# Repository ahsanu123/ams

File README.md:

<p>

</p>

 <details>
   <summary><h2>Shema</h2></summary>

 </details>
 
<sub> Work In Progress, Made With ❤️ By Ah...</sub>

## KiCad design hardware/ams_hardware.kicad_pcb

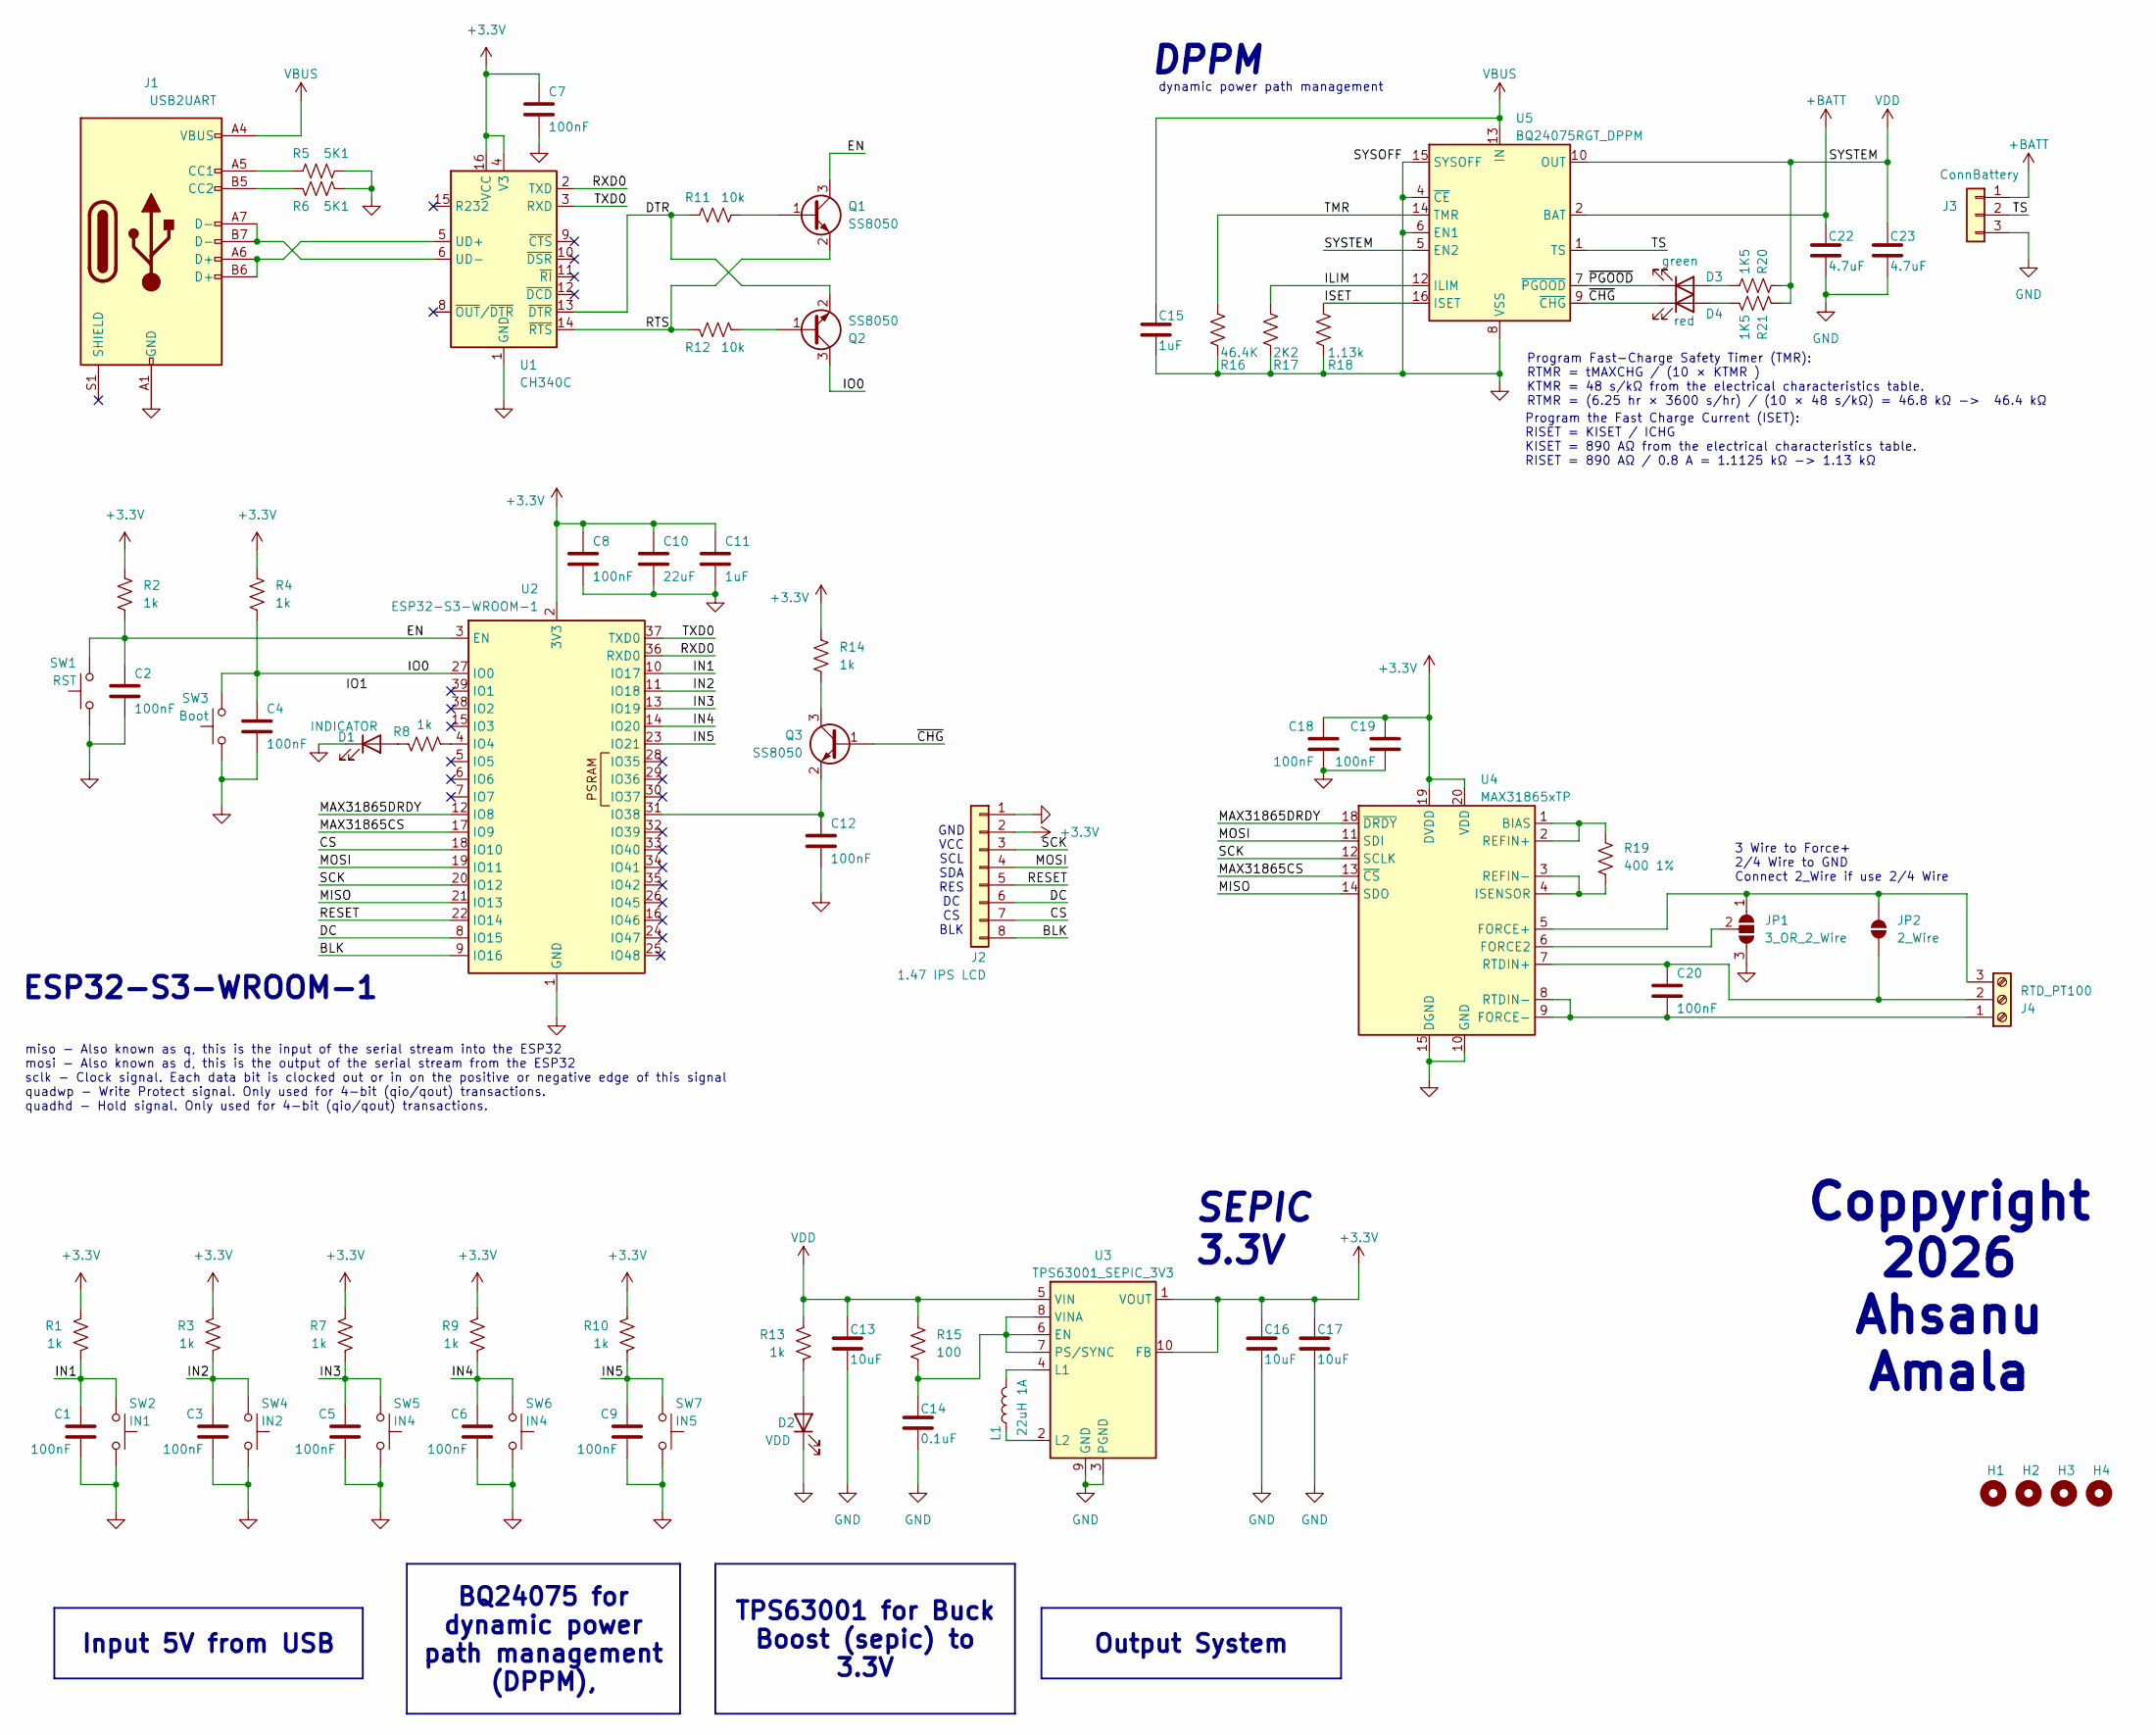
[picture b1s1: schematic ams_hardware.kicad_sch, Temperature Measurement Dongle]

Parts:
C1, C2, C3, C4, C5, C6, C7, C8, C9, C12, C18, C19, C20: 100nF; C_0805_2012Metric_Pad1.18x1.45mm_HandSolder
C10: 22uF; C_0805_2012Metric_Pad1.18x1.45mm_HandSolder
C11, C15: 1uF; C_0805_2012Metric_Pad1.18x1.45mm_HandSolder
C13, C16, C17: 10uF; C_0805_2012Metric_Pad1.18x1.45mm_HandSolder
C14: 0.1uF; C_0805_2012Metric_Pad1.18x1.45mm_HandSolder
C22, C23: 4.7uF; C_0805_2012Metric_Pad1.18x1.45mm_HandSolder
D1: INDICATOR; LED_1206_3216Metric_Pad1.42x1.75mm_HandSolder
D2: VDD; LED_1206_3216Metric_Pad1.42x1.75mm_HandSolder
D3: green; LED_0805_2012Metric_Pad1.15x1.40mm_HandSolder
D4: red; LED_0805_2012Metric_Pad1.15x1.40mm_HandSolder
H1, H2, H3, H4: MountingHole; MountingHole_2mm
J1: USB2UART; USB_C_Receptacle_GCT_USB4110
J2: 1.47 IPS LCD; PinHeader_1x08_P2.54mm_Vertical
J3: ConnBattery; PinHeader_1x03_P2.54mm_Vertical
J4: RTD_PT100; TerminalBlock_Phoenix_PT-1,5-3-5.0-H_1x03_P5.00mm_Horizontal
JP1: 3_OR_2_Wire; SolderJumper-3_P1.3mm_Open_RoundedPad1.0x1.5mm
JP2: 2_Wire; SolderJumper-2_P1.3mm_Open_TrianglePad1.0x1.5mm
L1: 22uH 1A; L_Bourns_SRP7028A_7.3x6.6mm
Q1, Q2, Q3: SS8050; SOT-23_Handsoldering
R1, R2, R3, R4, R7, R8, R9, R10, R13, R14: 1k; R_0805_2012Metric_Pad1.20x1.40mm_HandSolder
R5, R6: 5K1; R_0805_2012Metric_Pad1.20x1.40mm_HandSolder
R11, R12: 10k; R_0805_2012Metric_Pad1.20x1.40mm_HandSolder
R15: 100; R_0805_2012Metric_Pad1.20x1.40mm_HandSolder
R16: 46.4K; R_0805_2012Metric_Pad1.20x1.40mm_HandSolder
R17: 2K2; R_0805_2012Metric_Pad1.20x1.40mm_HandSolder
R18: 1.13k; R_0805_2012Metric_Pad1.20x1.40mm_HandSolder
R19: 400 1%; R_0805_2012Metric_Pad1.20x1.40mm_HandSolder
R20, R21: 1K5; R_0805_2012Metric_Pad1.20x1.40mm_HandSolder
SW1: RST; SW_SPST_PTS810
SW2: IN1; SW_SPST_Omron_B3FS-100xP
SW3: Boot; SW_SPST_PTS810
SW4: IN2; SW_SPST_Omron_B3FS-100xP
SW5, SW6: IN4; SW_SPST_Omron_B3FS-100xP
SW7: IN5; SW_SPST_Omron_B3FS-100xP
U1: CH340C; SOIC-16_3.9x9.9mm_P1.27mm
U2: ESP32-S3-WROOM-1
U3: TPS63001_SEPIC_3V3; Texas_DRC0010J_ThermalVias
U4: MAX31865xTP; TQFN-20-1EP_5x5mm_P0.65mm_EP3.25x3.25mm
U5: BQ24075RGT_DPPM; VQFN-16-1EP_3x3mm_P0.5mm_EP1.6x1.6mm

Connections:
+3.3V: C7.1, C8.1, C10.1, C11.1, C16.1, C17.1, C18.1, C19.1, J2.2, R1.1, R2.1, R3.1, R4.1, R7.1, R9.1, R10.1, R14.1, U1.4 (V3), U1.16 (VCC), U2.2 (3V3), U3.1 (VOUT), U3.10 (FB), U4.19 (DVDD), U4.20 (VDD)
+BATT: C22.1, J3.1, U5.2 (BAT), U5.3 (BAT)
/BLK: J2.8, U2.9 (IO16)
/CS: J2.7, U2.18 (IO10)
/DC: J2.6, U2.8 (IO15)
/DTR: Q2.2 (E), R11.2, U1.13 (~DTR)
/EN: C2.1, Q1.3 (C), R2.2, SW1.2, U2.3 (EN)
/ILIM: R17.1, U5.12 (ILIM)
/IN1: C1.1, R1.2, SW2.2, U2.10 (IO17)
/IN2: C3.1, R3.2, SW4.2, U2.11 (IO18)
/IN3: C5.1, R7.2, SW5.2, U2.13 (IO19)
/IN4: C6.1, R9.2, SW6.2, U2.14 (IO20)
/IN5: C9.1, R10.2, SW7.2, U2.23 (IO21)
/IO0: C4.1, Q2.3 (C), R4.2, SW3.2, U2.27 (IO0)
/ISET: R18.1, U5.16 (ISET)
/MAX31865CS: U2.17 (IO9), U4.13 (~CS)
/MAX31865DRDY: U2.12 (IO8), U4.18 (~DRDY)
/MISO: U2.21 (IO13), U4.14 (SDO)
/MOSI: J2.4, U2.19 (IO11), U4.11 (SDI)
/RESET: J2.5, U2.22 (IO14)
/RTS: Q1.2 (E), R12.2, U1.14 (~RTS)
/RXD0: U1.2 (TXD), U2.36 (RXD0)
/SCK: J2.3, U2.20 (IO12), U4.12 (SCLK)
/TMR: R16.1, U5.14 (TMR)
/TS: J3.2, U5.1 (TS)
/TXD0: U1.3 (RXD), U2.37 (TXD0)
/~CHG: D4.1 (K), Q3.1 (B), U5.9 (~CHG)
/~PGOOD: D3.1 (K), U5.7 (~PGOOD)
GND: C1.2, C2.2, C3.2, C4.2, C5.2, C6.2, C7.2, C8.2, C9.2, C10.2, C11.2, C12.2, C13.2, C14.2, C15.2, C16.2, C17.2, C18.2, C19.2, C22.2, C23.2, D1.1 (K), D2.1 (K), J1.A1 (GND), J1.A12 (GND), J1.B1 (GND), J1.B12 (GND), J2.1, J3.3, JP1.3 (B), R5.1, R6.1, R16.2, R17.2, R18.2, SW1.1, SW2.1, SW3.1, SW4.1, SW5.1, SW6.1, SW7.1, U1.1 (GND), U2.1 (GND), U2.40 (GND), U2.41 (GND), U3.3 (PGND), U3.9 (GND), U3.11 (PGND), U4.10 (GND), U4.15 (DGND), U4.16 (GND), U4.21 (GND), U5.4 (~CE), U5.6 (EN1), U5.8 (VSS), U5.15 (SYSOFF), U5.17 (VSS)
unnamed: D1.2 (A), R8.1
unnamed: D2.2 (A), R13.2
unnamed: D3.2 (A), R20.1
unnamed: D4.2 (A), R21.1
unnamed: J1.A5 (CC1), R5.2
unnamed: J1.B5 (CC2), R6.2
unnamed: C20.2, J4.1, U4.8 (RTDIN-), U4.9 (FORCE-)
unnamed: C20.1, J4.2, JP2.1 (A), U4.7 (RTDIN+)
unnamed: J4.3, JP1.1 (A), JP2.2 (B), U4.5 (FORCE+)
unnamed: JP1.2 (C), U4.6 (FORCE2)
unnamed: Q1.1 (B), R11.1
unnamed: Q2.1 (B), R12.1
unnamed: Q3.3 (C), R14.2
unnamed: C12.1, Q3.2 (E), U2.31 (IO38)
unnamed: J1.A6 (D+), J1.B6 (D+), U1.5 (UD+)
unnamed: J1.A7 (D-), J1.B7 (D-), U1.6 (UD-)
unnamed: R8.2, U2.4 (IO4)
unnamed: C14.1, R15.2, U3.6 (EN), U3.7 (PS/SYNC), U3.8 (VINA)
unnamed: L1.2, U3.4 (L1)
unnamed: L1.1, U3.2 (L2)
unnamed: R19.1, U4.1 (BIAS), U4.2 (REFIN+)
unnamed: R19.2, U4.3 (REFIN-), U4.4 (ISENSOR)
VBUS: C15.1, J1.A4 (VBUS), J1.A9 (VBUS), J1.B4 (VBUS), J1.B9 (VBUS), U5.13 (IN)
VDD: C13.1, C23.1, R13.1, R15.1, R20.2, R21.2, U3.5 (VIN), U5.5 (EN2), U5.10 (OUT), U5.11 (OUT)

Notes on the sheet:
dynamic power path management
GND VCC SCL SDA RES DC CS BLK
miso - Also known as q, this is the input of the serial stream into the ESP32 mosi - Also known as d, this is the output of the serial stream from the ESP32 sclk - Clock signal. Each data bit is clocked out or in on the positive or negative edge of this signal quadwp - Write Protect signal. Only us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
ESP32-S3-WROOM-1
Program the Fast Charge Current (ISET): RISET = KISET / ICHG KISET = 890 AΩ from the electrical characteristics table. RISET = 890 AΩ / 0.8 A = 1.1125 kΩ -> 1.13 kΩ
DPPM
3 Wire to Force+ 2/4 Wire to GND Connect 2_Wire if use 2/4 Wire
SEPIC 3.3V
Program Fast-Charge Safety Timer (TMR): RTMR = tMAXCHG / (10 × KTMR ) KTMR = 48 s/kΩ from the electrical characteristics table. RTMR = (6.25 hr × 3600 s/hr) / (10 × 48 s/kΩ) = 46.8 kΩ -> 46.4 kΩ
Output System
TPS63001 for Buck Boost (sepic) to 3.3V
Coppyright 2026 Ahsanu Amala
Input 5V from USB
BQ24075 for dynamic power path management (DPPM),

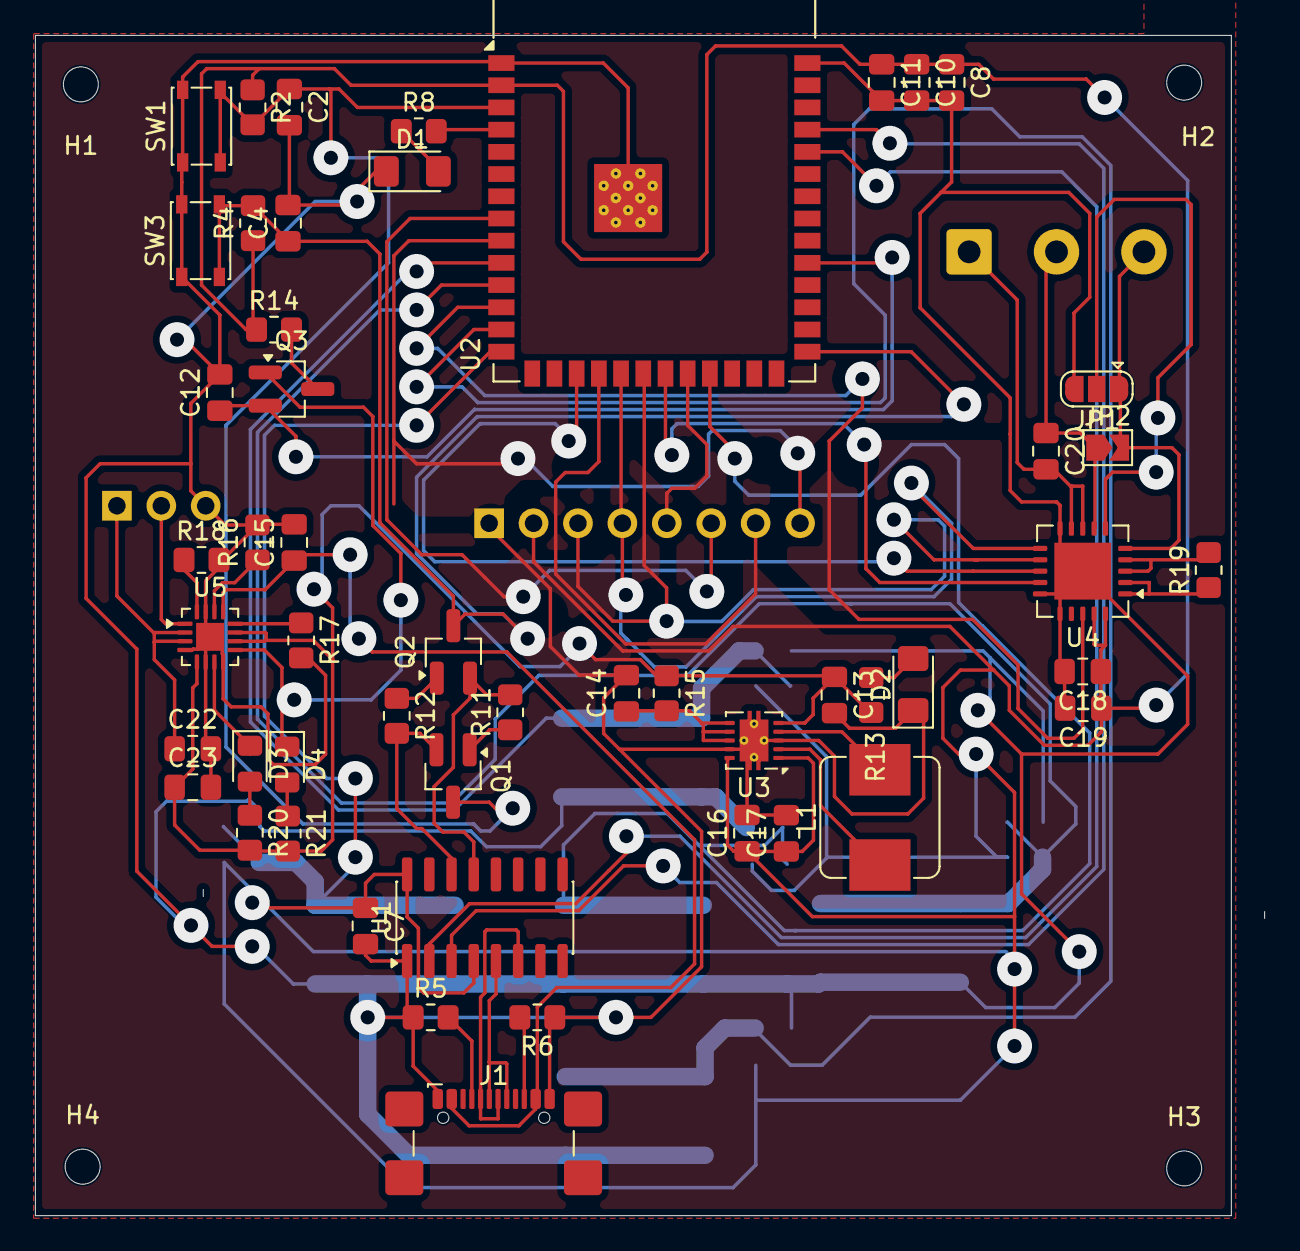
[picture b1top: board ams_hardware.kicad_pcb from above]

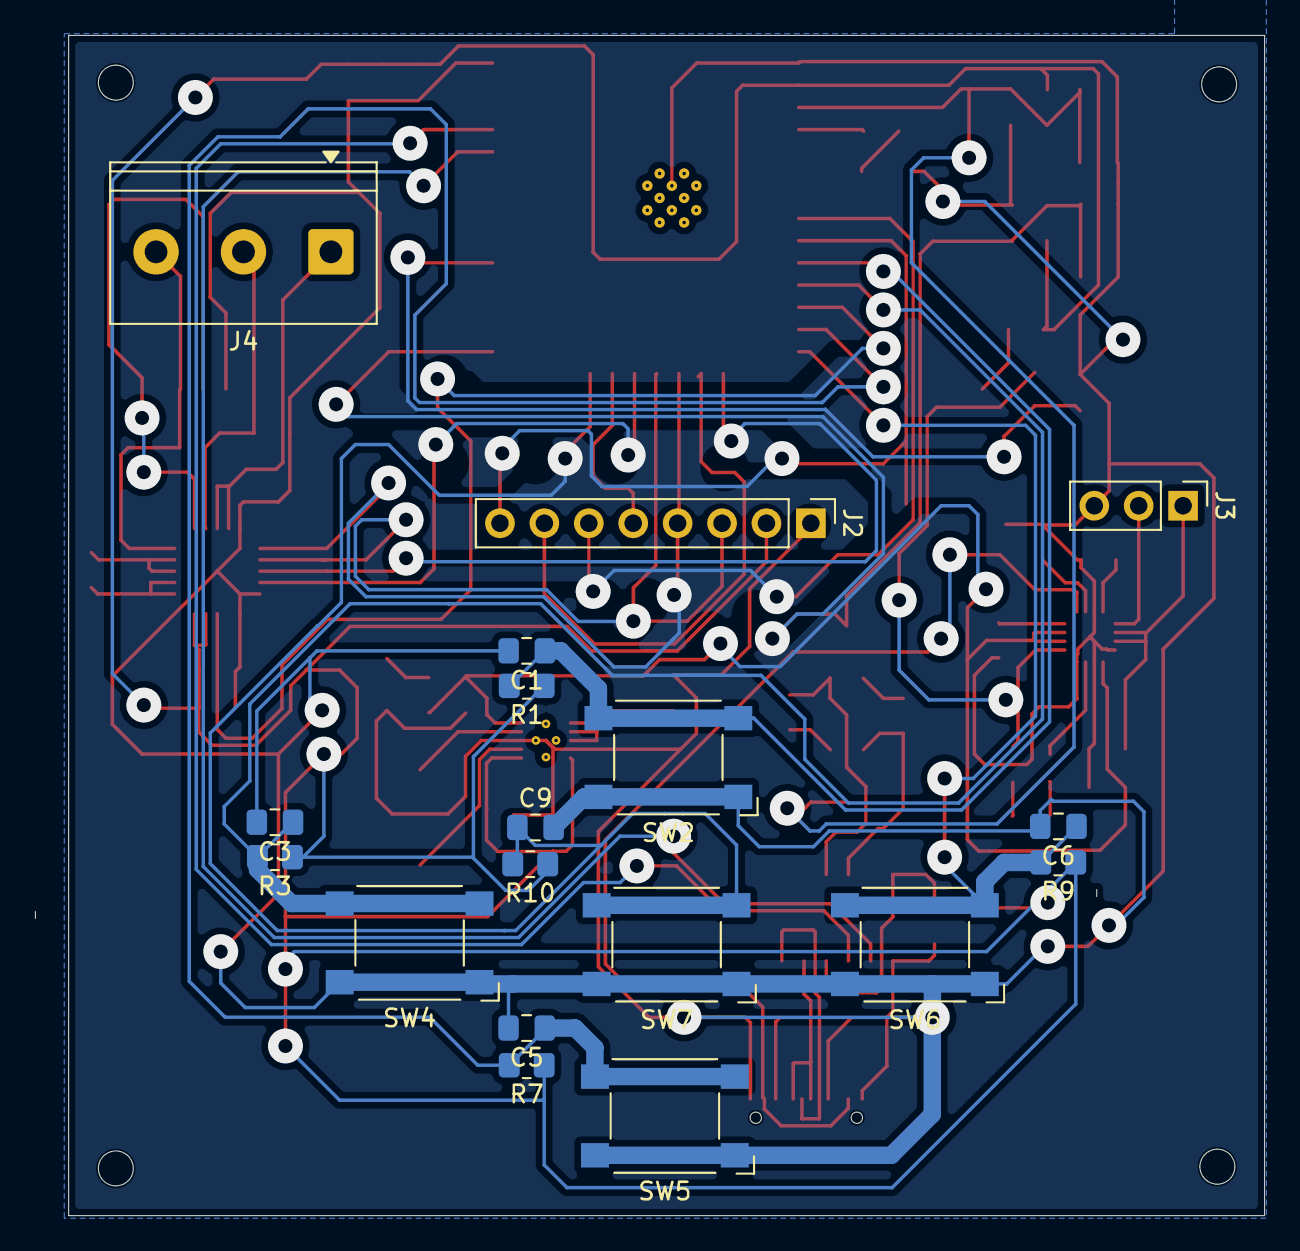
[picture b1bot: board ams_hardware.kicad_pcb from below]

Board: 2 copper layers, 70.3 x 67.5 mm, 73 parts (18 on the bottom side), 53 nets.

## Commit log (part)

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2025-01-07 [01-07-1640] ams moved from planerp-learn-auth
    Update README.md
2025-01-08 [01-07-1818] add QuestPdf to generate pdf report document
    update
    nit morning
2025-01-21 [01-21-1316] basic tauri setup worked
    nit
2025-01-21 [01-21-1316] add several file
    add migration
2025-01-21 [01-21-2037] update tauri config
2025-02-14 [02-14-1647] update on model and sql usage
2025-02-14 [02-14-2130] trying to create migrator with sqlx and sea-query builder
    nit, edit readme
2025-02-14 [02-14-2149] restructuring project
    fix several error, still many though
2025-02-18 [02-18-2050] basic creating database and insert worked with sea-query builder.
2025-02-19 [02-19-0811] create trait to ease define column and value when insert
2025-02-21 [02-21-1748] stuck with sea-query, trying to make with diesel
2025-02-24 [02-24-2036] night update on db connection pool and global environment variable
    nit
2025-02-24 [02-25-0459] turnout diesel was sync and not async, so its blocking...
    nit
2025-02-25 [02-25-0915] adding more confusion
    nit
    nit
2025-02-25 [02-25-1924] ok inserting with diesel and build table with sea-query is worked even its boiler plate compared to dotnet solution
    nit
2025-02-25 [02-25-2118] model and repository update
2025-02-26 [02-26-1605] basic up and down migration worked
    Update ams-logo.svg
    Update README.md
    Update README.md
2025-02-27 [02-27-0943] basic relation test with diesel and sea-query worked
2025-03-01 [03-01-2015] creating several table and make logic for app in notion
2025-03-08 [03-08-1154] reorganized project structure (again)
    nit
2025-03-09 [03-09-2046] finish product repositoy, next create command to hold function logic, or create diesel query to save complex query
    Update README.md
    Update README.md
    Update README.md
2025-03-10 [03-10-1515] remove unused repository
2025-03-11 [03-11-1546] work on user repository
    Update README.md
    Update README.md
2025-03-11 [03-11-1849] start work on command
    Update README.md
2025-03-11 [03-11-2004] mocking invoke and setup browser development
    nit
    Update README.md
2025-03-13 [03-13-2019] use react router 7 as framework (client side no ssr) as main ui
    nit
    Update README.md
2025-03-13 [03-13-2050] generating logo from squared image with cargo tauri icon
2025-03-15 [03-15-0936] setup vitest for component testing
    nit
    now vitest work,
2025-03-15 [03-15-1820] trying to refactor calendar and combine with product model (no success yet)
2025-03-16 [03-16-0901] calendar component is refactored
2025-03-16 [03-16-1159] remove un-needed old ui
2025-03-16 [03-16-1402] setup tauri to use same font as used in web
2025-03-16 [03-16-1528] build for production worked
    nit
2025-03-16 [03-16-1927] create admin guard for admin page
    Update README.md
2025-03-17 [03-17-1919] simple database metadata worked
2025-03-17 [03-17-2119] seed work, but dont know its cannot placed inside seeds/seeder folder
2025-03-20 [03-20-2120] hashed password in rust worked with argon2 library
2025-03-20 [03-20-2220] basic admin guard work with usenavigate from react router and cookie
2025-03-21 [03-22-0610] basic dialog display worked
2025-03-21 [03-22-0655] basic mock command workflow worked
2025-03-22 [03-22-0835] progress on edit product data page
    afternoon stuck
    Update README.md
2025-03-28 [03-28-2101] rename custom macro to ams_macro
    Update README.md
    remove unusded library after cross compile
2025-03-28 [03-28-2117] create test crate to test ams_macro
    create macro to generate struct with no id in it
    Update README.md
2025-04-07 [03-28-2117] create test crate to test ams_macro
    create macro to generate struct with no id in it
    Update README.md
    Update cross_compile.md
2025-04-13 [04-13-1903] add a lot of todo
2025-07-25 Create LICENSE
2025-07-25 [07-25-1857] actix-web hello world
2025-07-27 [07-27-1248] basic migration work for sqlite
2025-07-27 [07-27-1305] moving some folder
2025-07-27 [07-27-1322] refactor macro
2025-07-27 [07-27-1530] create models
2025-07-28 [07-28-0936] basic up and down migration work
    create crud with diesel again
2025-07-28 [07-28-1544] afternoon commit
2025-08-01 night stuck burnout
2025-08-03 [08-03-2031] continue trying to implement abstract repository with diesel rust
2025-09-19 chore: just stuck and think to use derive macro instead of extending diesel
2025-09-19 chore: attempt to create generic repository again.
2025-09-19 feat: add sea-orm migration project.
2025-09-20 feat: add several new table
2025-09-20 feat: add foreign key to table
2025-09-20 feat: generating entity from model
2025-09-20 feat: basic entity generation directly from src-tauri
    nit
2025-09-20 feat: connection string from env worked
2025-09-20 chore: correcting connection string for sea-orm
2025-09-21 feat: add basic connection and get_by_id structure
2025-09-21 feat: basic create and insert of abstract repository is work
    n
2025-09-21 feat: abstract repository for all sea-orm Entity type is worked
    n
2025-09-21 feat: remove old model and add password hash
2025-09-21 feat: morning update on theme
2025-09-22 feat: middle day update, but burnout
2025-09-22 feat: add sevearal sub pages
    nit
2025-09-22 feat: restructuring logic into shared, working with tauri is really slow, so split may improve performance when development
2025-09-22 feat: update several frontend component
2025-09-22 chore: add ams.sqlite to api by copying from migration
2025-09-23 feat: night update on command
2025-09-24 feat: setup basic test with vitest
2025-09-24 feat: basic navigation menu worked, need improvement
2025-09-24 feat: update on taking record
2025-09-25 feat: make progress on several repositories and command
    n
2025-09-25 feat: basic api call worked,
2025-10-02 feat: update test and make seed
2025-10-02 feat: change user management to use model rather than active model
2025-10-05 feat: add basic endpoint and service register
2025-10-05 feat: utoipa endpoint documentation
2025-10-05 feat: add utoipa swagger-ui actix enpoint
2025-10-05 feat: connecting api enpoint to command
2025-10-05 feat: add request_body in utoipa::path
2025-10-06 feat: add api endpoint to frontend
2025-10-13 feat: add model
2025-10-13 chore: update readme
2025-10-13 feat: basic api test working
2025-10-13 feat: add endpoint placeholder to front end
2025-10-13 feat: add asConstant
2025-10-13 feat: testing on swagger work
2025-10-15 feat: update generatecalendarobject to sum all amount
2025-10-17 feat: create tree menu for admin menus display
2025-10-18 feat: progress on makepayment page
2025-10-20 feat: make payment basic logic is work
2025-10-21 attempt to create payment list page
2025-11-15 feat(ui): change react component to use Chakra UI
2025-11-16 feat(ui): implement several mock page
2025-11-18 fix(api-docs): swagger endpoint model reference
2025-11-18 feat(docs): add swagger endpoint tag name
2025-11-18 feat(page): update taking page first iteration
2025-11-19 feat(page): user management page update first iteration
2025-11-20 feat(page): customer money iteration 1
2025-11-20 feat(page): finish customer money and delete customer iteration 2
2025-11-20 chore: Update README.md
2025-11-21 feat(tauri): adding tauri::command from shared package
2025-11-21 feat(page): add about page and what envrontment is
2025-11-21 feat: setup env to use onecell
2025-11-21 feat: builded and able to run on linux, but routing seem not work, need to investigate
2025-11-21 chore: add rename_all = "snake_case" to all tauri::command
2025-11-26 attempt to fix embedded resource is not readable
2025-11-26 feat: add logger to project
2025-11-27 feat: use same location db rather than embedded file
    n
2025-11-28 feat: add github workflow to build no bundle on push release branch
    n
2025-11-28 feat: add github workflow to build no bundle on push release branch
2025-11-28 feat: add endpoint to get taking record by range month
2025-11-29 feat: add basic structure of tanstack react router inside usermanagementcommand
2025-11-30 feat: create several use command
2025-11-30 chore: remove and rename unused file
2025-11-30 feat: update about message and select component
    Update README.md
2025-12-02 fix: small bug in password calculator
2025-12-02 chore: refactor ui to use chakra component
2025-12-02 feat: add more detail to make payment tab
2025-12-12 feat: update customer taking page to use react query logic
2025-12-12 feat: update make payment page to use react query
    lazy update
2025-12-12 feat: use add_taking_record_and_date
2025-12-13 feat: morning update
2025-12-20 feat: move copyright and increase font size
2025-12-21 feat: add onKeypress in <Keyboard/>, see if it work on touch screen
2025-12-21 feat: change default tab in make payment to calendar
2026-01-02 feat: add script to auto backup and reboot on schedule
2026-01-02 chore: update github workflow script
2026-01-06 feat: add start sway script
2026-01-06 feat: create script to auto exit sway after 10 pm
2026-01-07 chore: update tauri.conf
    chore: update tauri.conf
2026-01-07 chore: update tauri.conf
2026-02-02 feat: start to create casing
2026-02-03 feat: create several singleton to expose shared API
2026-02-03 feat: update api to use latest shared code
2026-02-03 feat: refactor shared to use "self" part 1
2026-02-03 feat: update tauri command to use shared code
2026-02-03 feat: start ams server on tauri application
    nit
2026-02-03 feat: create incubator folder to test run builded no bundle on dev computer
2026-02-03 feat: enable static file service
2026-02-05 feat: get static file path from .env
2026-02-17 feat: migrate seaql migration to version 2.0
2026-02-17 feat: entity is builded successfully
2026-02-17 feat: attempt to refactor generic repository
2026-02-18 feat: implement data_record model
2026-02-18 feat: create several repositories placeholder
2026-02-19 feat: add create and read in retrieve data repository
2026-02-21 feat: create billing repository
2026-02-21 feat: add basic structure to use statement with stored procedure as file with include_str() function
2026-02-23 feat: create billing create and read
2026-02-23 feat: add update method to billing
2026-02-25 feat: create balance repository
2026-02-25 feat: create balance billing repository
2026-02-25 chore: renaming commands to controllers
2026-02-25 feat: create customer controller
2026-02-25 feat: create dreg price controller
2026-02-27 feat: add ts-rs feature to auto generate typescript model
2026-02-27 feat: create DataRecordController
2026-02-27 feat: create retrieve data controller
2026-02-28 feat: stupidly change component library
2026-02-28 feat: re-create calendar object and calendar component
2026-02-28 feat: create basic layout with grid
2026-03-01 feat: create sidebar logic routing
2026-03-01 chore: renaming several model
2026-03-01 feat: create shared function assign_to_parent and assign_to_parent_arr
2026-03-01 feat: add retrieve data endpoint to create and create with date
2026-03-02 feat: add update, delete and get endpoint in retrieve data controller
2026-03-03 feat: create customer management controller
2026-03-03 feat: add several endpoint in balance controller
2026-03-04 feat: completing get all in balance controller
2026-03-04 chore: need to add operand_id for every endpoint
2026-03-05 feat: add several endpoint to billing info controller
2026-03-06 feat: add several get_by endpoint
2026-03-06 feat: add get all billing to billing repo
2026-03-07 feat: add orval to automatic generate api in frontend from openapi specification
2026-03-08 feat: add orval to automatic generate api in frontend
2026-03-09 feat: add price controller
2026-03-10 feat: connecting retrieve data to backend
2026-03-10 chore: rename mantine-app to app
2026-03-10 feat: create basic right sidebar routing
2026-03-11 fix: build with new library
2026-03-18 feat: remove build on armv7 on github action
2026-03-18 chore: remove old-app
2026-04-22 chore: removing several old code
2026-04-22 feat: init ams hardware
2026-04-22 feat: add hardware_libraries
2026-04-22 feat: add pi zero 2 w in schematic
